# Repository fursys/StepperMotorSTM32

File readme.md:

please use em::blocks IDE to easy open this project.
You can find motor driver schematic and PCB layout in HardwareUnipolar folder
I'm using 12MHz crystal oscillator in my projects (please change value in line 1067 of system_stm32f10x.c file or replace the file completely)

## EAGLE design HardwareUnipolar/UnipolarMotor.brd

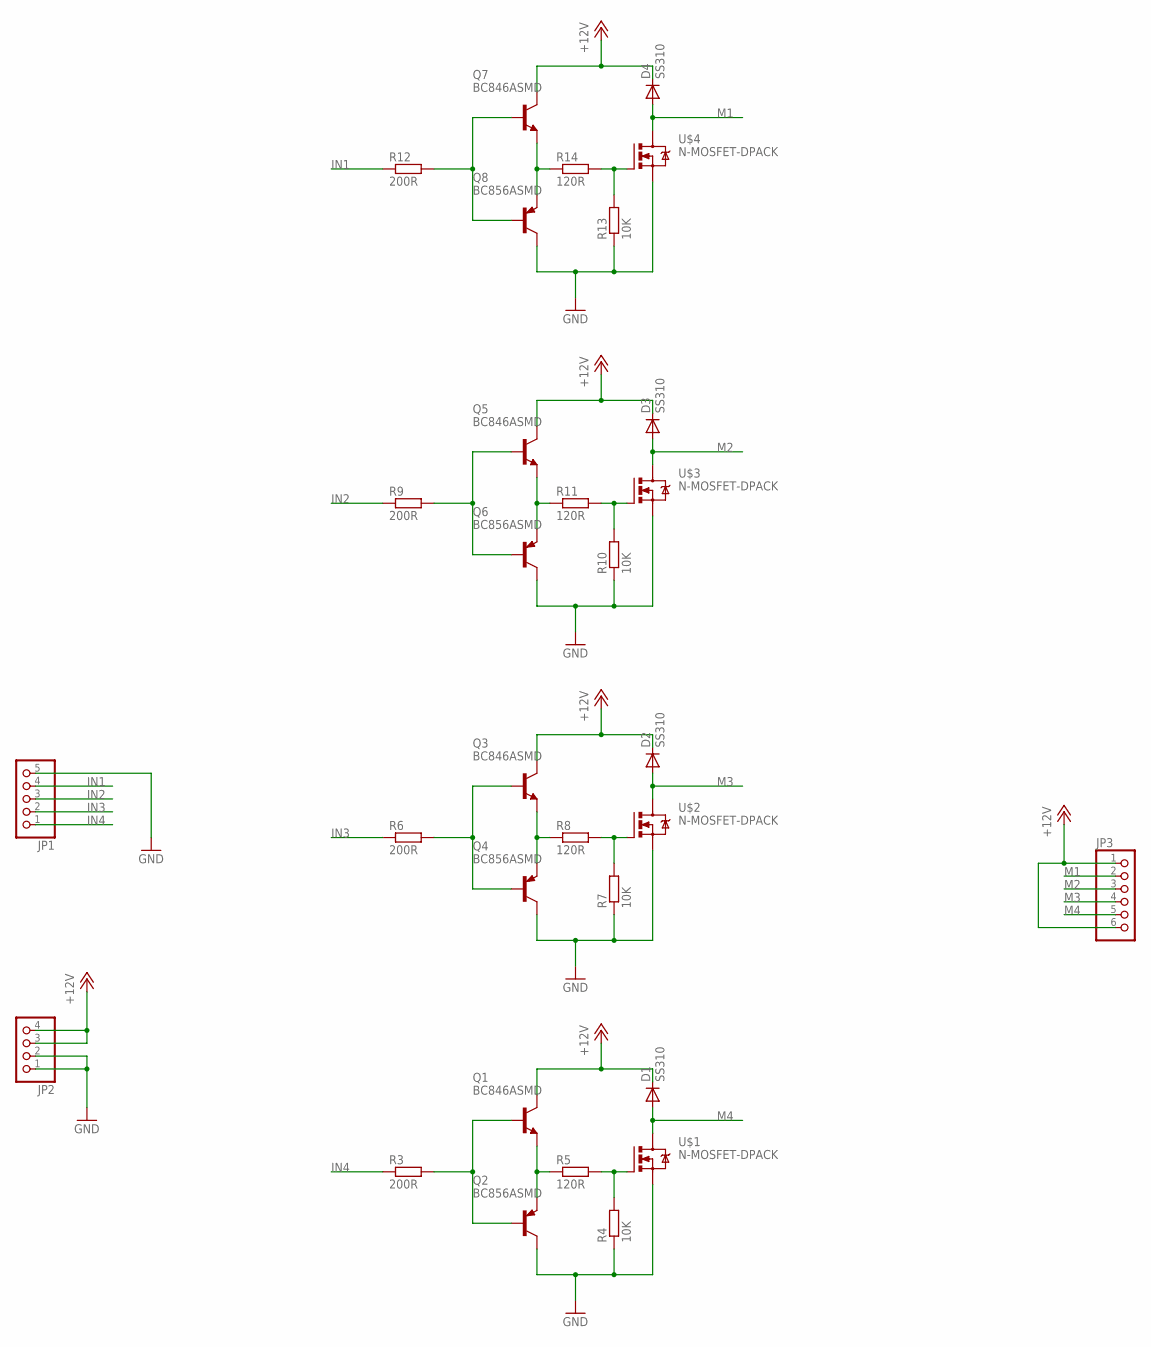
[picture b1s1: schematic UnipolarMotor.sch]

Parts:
D1, D2, D3, D4: SS310; SMA-DIODE_ALT
JP1: PINHD-1X5; 1X05
JP2: PINHD-1X4; 1X04
JP3: PINHD-1X6; 1X06
Q1, Q3, Q5, Q7: BC846ASMD; SOT23
Q2, Q4, Q6, Q8: BC856ASMD; SOT23-BEC
R3, R6, R9, R12: 200R; 0204/7
R4, R7, R10, R13: 10K; R0805
R5, R8, R11, R14: 120R; R0805
U$1, U$2, U$3, U$4: N-MOSFET-DPACK; DPACK

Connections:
+12V: D1.C, D2.C, D3.C, D4.C, JP2.3, JP2.4, JP3.1, JP3.6, Q1.3 (C), Q3.3 (C), Q5.3 (C), Q7.3 (C)
GND: JP1.5, JP2.1, JP2.2, Q2.C, Q4.C, Q6.C, Q8.C, R4.1, R7.1, R10.1, R13.1, U$1.3 (S), U$2.3 (S), U$3.3 (S), U$4.3 (S)
IN1: JP1.4, R12.1
IN2: JP1.3, R9.1
IN3: JP1.2, R6.1
IN4: JP1.1, R3.1
M1: D4.A, JP3.2, U$4.2 (D)
M2: D3.A, JP3.3, U$3.2 (D)
M3: D2.A, JP3.4, U$2.2 (D)
M4: D1.A, JP3.5, U$1.2 (D)
unnamed: Q1.2 (E), Q2.E, R5.1
unnamed: R4.2, R5.2, U$1.1 (G)
unnamed: Q1.1 (B), Q2.B, R3.2
unnamed: Q3.2 (E), Q4.E, R8.1
unnamed: R7.2, R8.2, U$2.1 (G)
unnamed: Q3.1 (B), Q4.B, R6.2
unnamed: Q5.2 (E), Q6.E, R11.1
unnamed: R10.2, R11.2, U$3.1 (G)
unnamed: Q5.1 (B), Q6.B, R9.2
unnamed: Q7.2 (E), Q8.E, R14.1
unnamed: R13.2, R14.2, U$4.1 (G)
unnamed: Q7.1 (B), Q8.B, R12.2

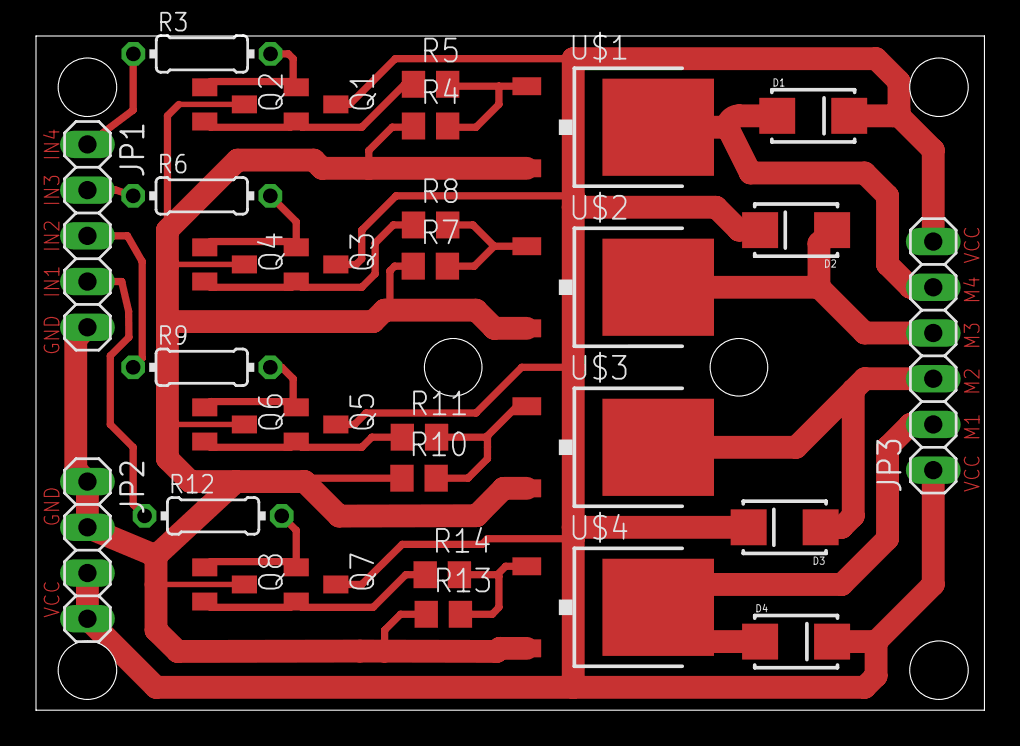
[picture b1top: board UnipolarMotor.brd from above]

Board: 2 copper layers, 52.7 x 37.5 mm, 31 parts (0 on the bottom side), 22 nets.

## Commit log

2015-01-07 Readme update

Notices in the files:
parts and their libraries:
SparkFun: Licensing: CC v3.0 Share-Alike You are welcome to use this library for commercial purposes.
